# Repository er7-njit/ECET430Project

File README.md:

# GPS Tracker Project
Eliyahu Richter and Ravyn John's ECET 430 Project

Our initial **Project Definition** is available [here](https://github.com/er7-njit/GPSTracker430/blob/main/Documentation/Initial%20Project%20Definition.pdf)

Our final **Project Definition** is available [here](https://github.com/er7-njit/GPSTracker430/blob/main/Documentation/Final%20Project%20Definition.pdf)

A summary of our **Component Decisions** is available [here](https://github.com/er7-njit/GPSTracker430/blob/main/Documentation/Design%20decision.pdf)

**Documentation** is available [here](https://github.com/er7-njit/GPSTracker430/blob/main/Documentation/Documentation.md)

The **Logbook** for the project's progress is [here](https://github.com/er7-njit/GPSTracker430/wiki/Logbook)

Our **Project Files** are [here](https://github.com/er7-njit/GPSTracker430/tree/main/PCB%20Design)

Most questions about our project can be answered by the [wiki](https://github.com/er7-njit/GPSTracker430/wiki)

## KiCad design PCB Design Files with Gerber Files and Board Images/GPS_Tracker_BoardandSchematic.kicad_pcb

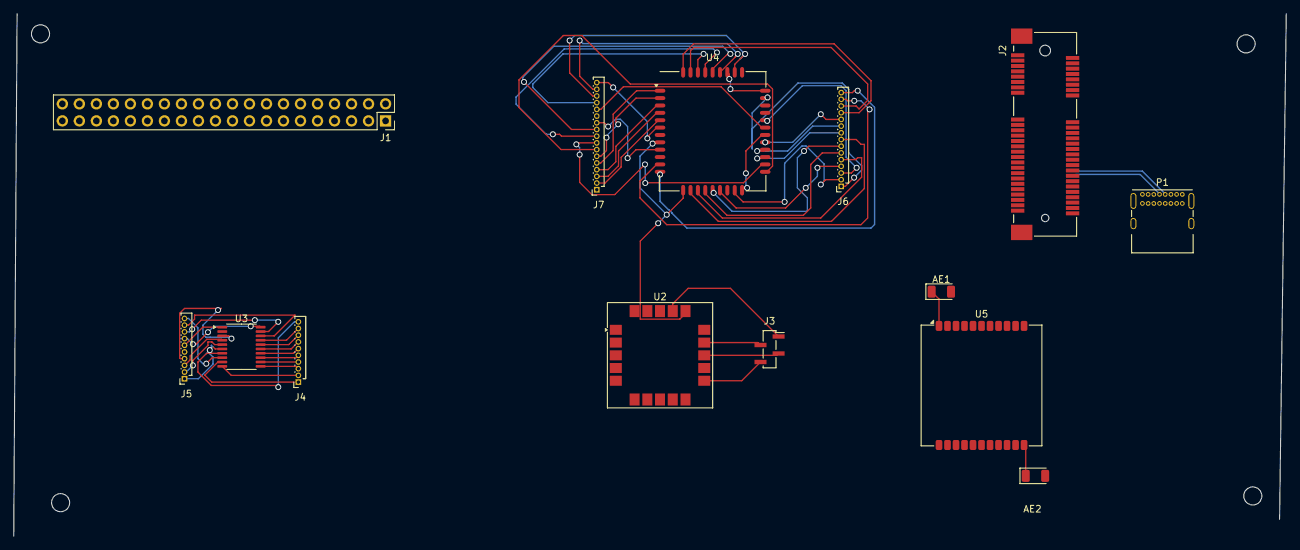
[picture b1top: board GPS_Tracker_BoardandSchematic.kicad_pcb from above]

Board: 2 copper layers, 190.0 x 78.0 mm, 18 parts (0 on the bottom side), 60 nets.

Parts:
AE1, AE2: Antenna; Johanson_2450AT18x100
J1: GPIO; PinSocket_2x20_P2.54mm_Vertical
J2: Bus_PCI_Express_Mini; BUS_PCI_Express_Mini
J3: Conn_01x04_Socket; PinSocket_1x04_P1.27mm_Vertical_SMD_Pin1Right
J4, J5: Conn_01x10_Socket; PinSocket_1x10_P1.00mm_Vertical
J6: Conn_01x15_Socket; PinSocket_1x15_P1.00mm_Vertical
J7: Conn_01x17_Socket; PinSocket_1x17_P1.00mm_Vertical
MH1, MH2, MH3, MH4: MountingHole_2.7mm_M2.5
P1: USB_C_Plug_USB2.0; USB_C_Receptacle_GCT_USB4085
U2: SAM-M8Q; ublox_SAM-M8Q
U3: CH32V003FxPx; TSSOP-20_4.4x6.5mm_P0.65mm
U4: SIM800C; SIMCom_SIM800C
U5: HT-CT62; Heltec_HT-CT62

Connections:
+3V3: J1.1, J1.17
+5V: J1.2, J1.4
GND: J1.6, J1.9, J1.14, J1.20, J1.25, J1.30, J1.34, J1.39, J3.4, J7.16, U2.1 (GND), U2.4 (GND), U2.5 (GND), U2.6 (GND), U2.10 (GND), U2.11 (GND), U2.15 (GND), U2.16 (GND), U2.20 (GND), U4.8 (GND), U4.13 (GND), U4.19 (GND), U4.21 (GND), U4.27 (GND), U4.30 (GND), U4.31 (GND), U4.33 (GND), U4.36 (GND), U4.37 (GND)
unnamed: AE1.1 (A), U5.1 (2.4G_Ant)
unnamed: AE2.1 (A), U5.22 (LoRa_Ant)
unnamed: J2.38 (USB_D+), P1.A6 (D+)
unnamed: J2.36 (USB_D-), P1.A7 (D-)
unnamed: J3.1, U2.17 (VCC)
unnamed: J3.2, U2.14 (RXD)
unnamed: J3.3, U2.13 (TXD)
unnamed: J4.1, U3.9 (VDD)
unnamed: J4.2, U3.10 (PC0)
unnamed: J4.3, U3.11 (PC1)
unnamed: J4.4, U3.12 (PC2)
unnamed: J4.5, U3.13 (PC3)
unnamed: J4.6, U3.14 (PC4)
unnamed: J4.7, U3.15 (PC5)
unnamed: J4.8, U3.16 (PC6)
unnamed: J4.9, U3.17 (PC7)
unnamed: J4.10, U3.7 (VSS)
unnamed: J5.1, U3.6 (PA2)
unnamed: J5.2, U3.5 (PA1)
unnamed: J5.3, U3.4 (PD7)
unnamed: J5.4, U3.3 (PD6)
unnamed: J5.6, U3.1 (PD4)
unnamed: J5.7, U3.20 (PD3)
unnamed: J5.8, U3.19 (PD2)
unnamed: J5.9, U3.18 (PD1)
unnamed: J5.10, U3.8 (PD0)
unnamed: J6.1, U4.32 (GSM_ANT)
unnamed: J6.2, U4.20 (BT_ANT)
unnamed: J6.3, U4.29 (RF_SYNC)
unnamed: J6.4, U4.18 (SIM_VDD)
unnamed: J6.5, U4.15 (SIM_DATA)
unnamed: J6.6, U4.16 (SIM_CLK)
unnamed: J6.7, U4.17 (SIM_RST)
unnamed: J6.8, U4.14 (SIM_DET)
unnamed: J6.9, U4.24 (USB_VBUS)
unnamed: J6.10, U4.25 (USB_DP)
unnamed: J6.11, U4.26 (USB_DM)
unnamed: J6.12, U4.42 (STATUS)
unnamed: J6.13, U4.41 (NETLIGHT)
unnamed: J6.14, U4.11 (SPKP)
unnamed: J6.15, U4.12 (SPKN)
unnamed: J7.1, U4.7 (UART1_RI)
unnamed: J7.2, U4.5 (UART1_DCD)
unnamed: J7.3, U4.4 (UART1_CTS)
unnamed: J7.4, U4.3 (UART1_RTS)
unnamed: J7.5, U4.1 (UART1_TXD)
unnamed: J7.6, U4.2 (UART1_RXD)
unnamed: J7.7, U4.22 (UART2_TXD)
unnamed: J7.8, U4.23 (UART2_RXD)
unnamed: J7.9, U4.39 (~PWRKEY)
unnamed: J7.10, U4.38 (ADC)
unnamed: J7.11, U4.9 (MICP)
unnamed: J7.12, U4.10 (MICN)
unnamed: J7.13, U4.28 (VRTC)
unnamed: J7.14, U4.40 (VDD_EXT)
unnamed: J7.15, U4.34 (VBAT), U4.35 (VBAT)
unnamed: J7.17, U4.6 (UART1_DTR)

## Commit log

2024-12-22 Create BOM
    find the bom list here
2024-12-22 Create Test
2024-12-22 Renamed to older version
2024-12-22 renamed code to scripts for clarity
2024-12-22 Update README.md
    added pics
2024-12-23 Update README.md
    changed location of documentation
2024-12-23 Update Documentation.md
    update 2
2024-12-23 Delete Scripts/basefile.md
    file was placeholder
2024-12-23 Rename Tracker Project Definition-1.pdf to Initial Project Definition.pdf
2024-12-23 Create placeholder
